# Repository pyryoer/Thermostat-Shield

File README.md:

Thermostat-Shield
=================

Shield for Spark core for Thermostat with 24V AC power supply

* [Firmware](https://github.com/mumblepins/core-firmware)
* [Server](https://github.com/mumblepins/ThermostatServer)
* [Shield](https://github.com/mumblepins/Thermostat-Shield)

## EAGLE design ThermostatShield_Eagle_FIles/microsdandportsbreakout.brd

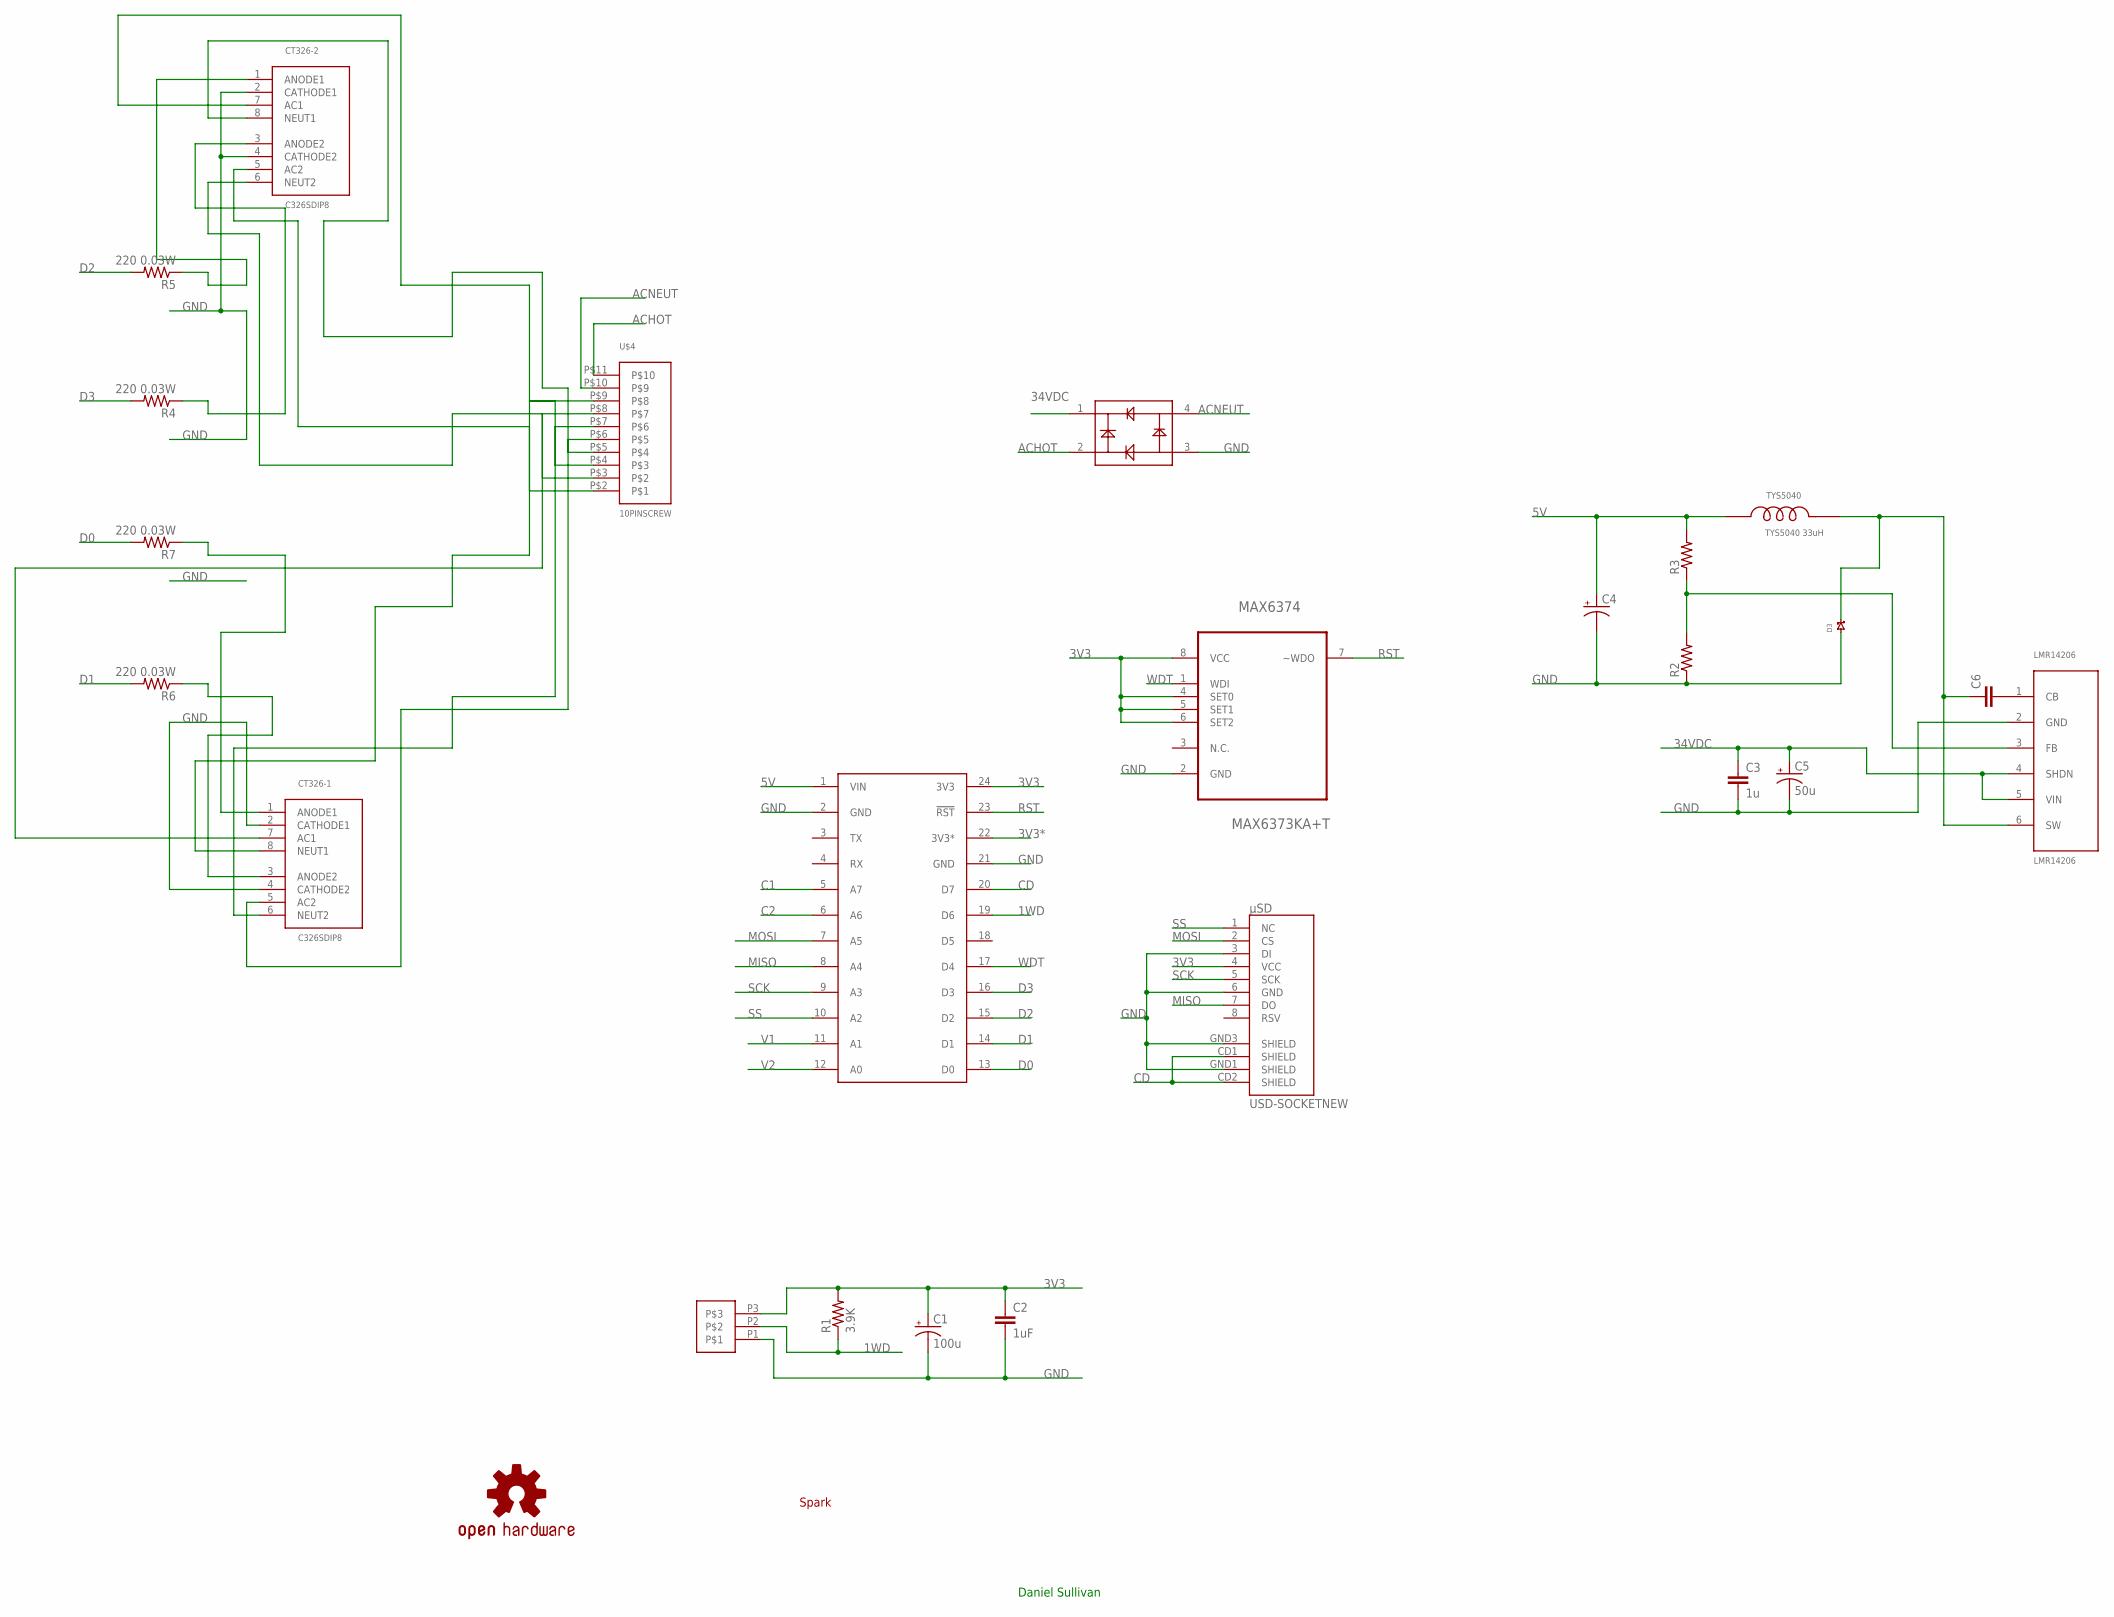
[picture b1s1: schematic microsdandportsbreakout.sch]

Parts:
BRDG: BGX50A-BRIDGE; SOT143
C1: 100u; CPOL-5MM-PTH
C2: 1uF; 0603-CAP
C3: 1u; 0603-CAP
C4: CAP_POLRADIAL-5MM; CPOL-5MM-PTH
C5: 50u; ESK476M063AE3AA
C6: CAP0402-CAP; 0402-CAP
CT326-1, CT326-2: C326SDIP8; DIP08
D3: DIODE[SCHOTKY]-SOD123W; SOD123W
GND: SPARK_LOGO; SPARK_LOGO_TSTOP
LMR14206: LMR14206; SOT23-6
LOGO1: OSHW-LOGOS; OSHW-LOGO-S
MAX6374: MAX6373KA+T; SOT65P280X145-8N
R1: 3.9K; 0603
R2, R3: RESISTOR0402; 0402-RES
R4, R5, R6, R7: 220 0.03W; 0603-RES
SPARKCORE: SPARK_CORECORE; SPARK_CORE
TYS5040: TYS5040 33uH; LAIRD-TYS5040
U$4: 10PINSCREW; 10PIN-SCREW
U$6: SCREW3PIN; SCREW-3PIN
µSD: USD-SOCKETNEW; MICRO-SD-SOCKET-PP

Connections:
1WD: R1.1, SPARKCORE.19 (D6), U$6.P2
3V3: C1.+, C2.1, MAX6374.4 (SET0), MAX6374.5 (SET1), MAX6374.6 (SET2), MAX6374.8 (VCC), R1.2, SPARKCORE.24 (3V3), U$6.P3, µSD.4 (VCC)
3V3*: SPARKCORE.22 (3V3*)
5V: C4.+, R3.2, SPARKCORE.1 (VIN), TYS5040.P$2
11: CT326-1.5 (AC2), U$4.P$6
34VDC: BRDG.1, C3.1, C5.+, LMR14206.4 (SHDN), LMR14206.5 (VIN)
326: CT326-2.5 (AC2), U$4.P$2
352: CT326-2.7 (AC1), U$4.P$4
ACHOT: BRDG.2, U$4.P$11
ACNEUT: BRDG.4, U$4.P$10
C1: SPARKCORE.5 (A7)
C2: SPARKCORE.6 (A6)
CD: SPARKCORE.20 (D7), µSD.CD1 (SHIELD), µSD.CD2 (SHIELD)
D0: R7.2, SPARKCORE.13 (D0)
D1: R6.2, SPARKCORE.14 (D1)
D2: R5.2, SPARKCORE.15 (D2)
D3: R4.2, SPARKCORE.16 (D3)
FHS: CT326-1.7 (AC1), U$4.P$8
GND: BRDG.3, C1.-, C2.2, C3.2, C4.-, C5.-, CT326-1.2 (CATHODE1), CT326-1.4 (CATHODE2), CT326-2.2 (CATHODE1), CT326-2.4 (CATHODE2), D3.P$1 (1), LMR14206.2 (GND), MAX6374.2 (GND), R2.1, SPARKCORE.2 (GND), SPARKCORE.21 (GND), U$6.P1, µSD.3 (DI), µSD.6 (GND), µSD.GND1 (SHIELD), µSD.GND3 (SHIELD)
MISO: SPARKCORE.8 (A4), µSD.7 (DO)
MOSI: SPARKCORE.7 (A5), µSD.2 (CS)
unnamed: C6.2, LMR14206.1 (CB)
unnamed: C6.1, D3.P$2 (2), LMR14206.6 (SW), TYS5040.P$1
unnamed: CT326-2.6 (NEUT2), U$4.P$3
unnamed: CT326-1.1 (ANODE1), R7.1
unnamed: CT326-1.8 (NEUT1), U$4.P$9
unnamed: CT326-2.3 (ANODE2), R4.1
unnamed: CT326-1.3 (ANODE2), R6.1
unnamed: LMR14206.3 (FB), R2.2, R3.1
unnamed: CT326-2.1 (ANODE1), R5.1
unnamed: CT326-2.8 (NEUT1), U$4.P$5
unnamed: CT326-1.6 (NEUT2), U$4.P$7
RST: MAX6374.7 (~WDO), SPARKCORE.23 (!RST)
SCK: SPARKCORE.9 (A3), µSD.5 (SCK)
SS: SPARKCORE.10 (A2), µSD.1 (NC)
V1: SPARKCORE.11 (A1)
V2: SPARKCORE.12 (A0)
WDT: MAX6374.1 (WDI), SPARKCORE.17 (D4)

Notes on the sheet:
Daniel Sullivan

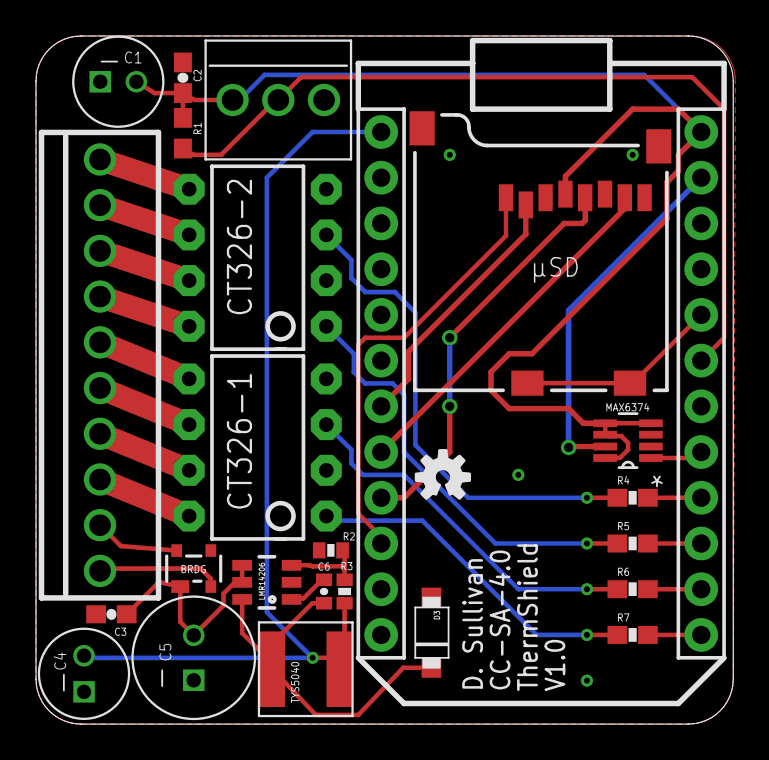
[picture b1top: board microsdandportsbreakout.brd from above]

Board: 2 copper layers, 38.7 x 38.2 mm, 26 parts (0 on the bottom side), 33 nets.

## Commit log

2014-06-11 Added links to other parts of project

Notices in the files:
ThermostatShield_Eagle_FIles/microsdandportsbreakout.brd:
Creative Commons-ShareAlike 4.0
parts and their libraries:
SparkFun-Capacitors: Licensing: Creative Commons ShareAlike 4.0 International - https://creativecommons.org/licenses/by-sa/4.0
